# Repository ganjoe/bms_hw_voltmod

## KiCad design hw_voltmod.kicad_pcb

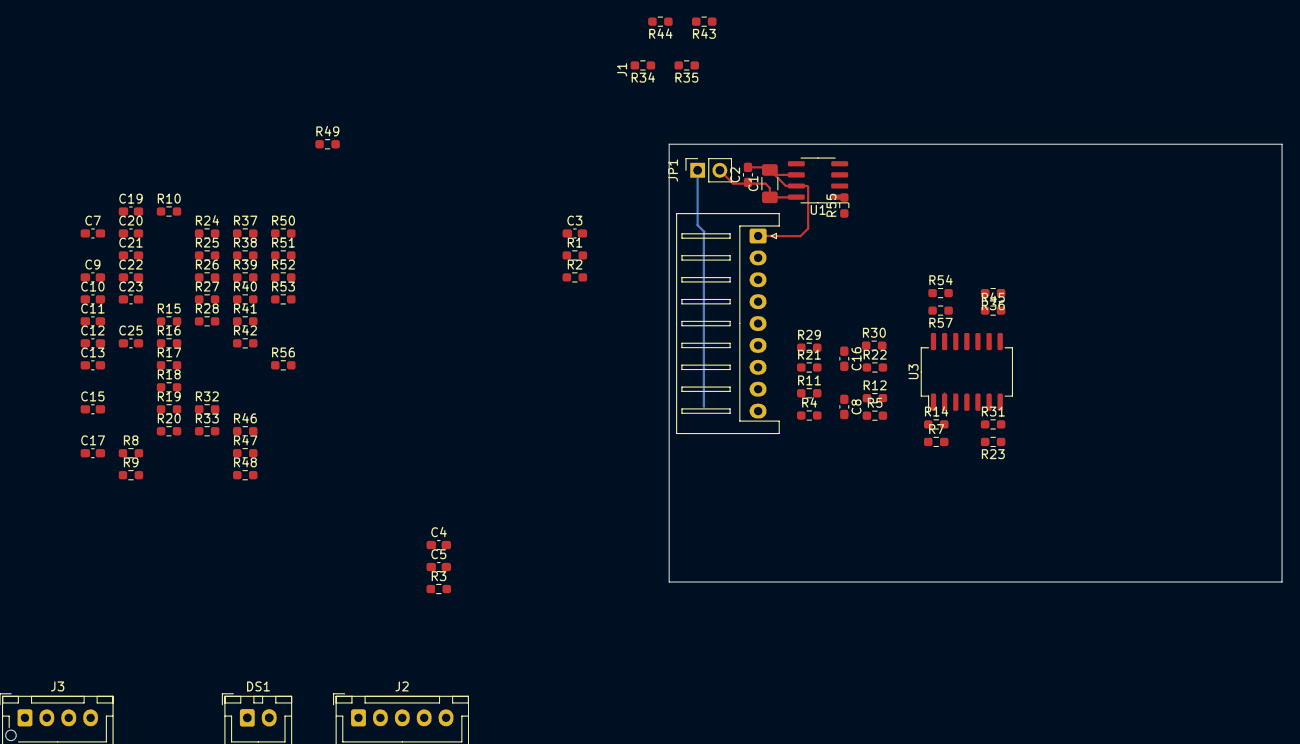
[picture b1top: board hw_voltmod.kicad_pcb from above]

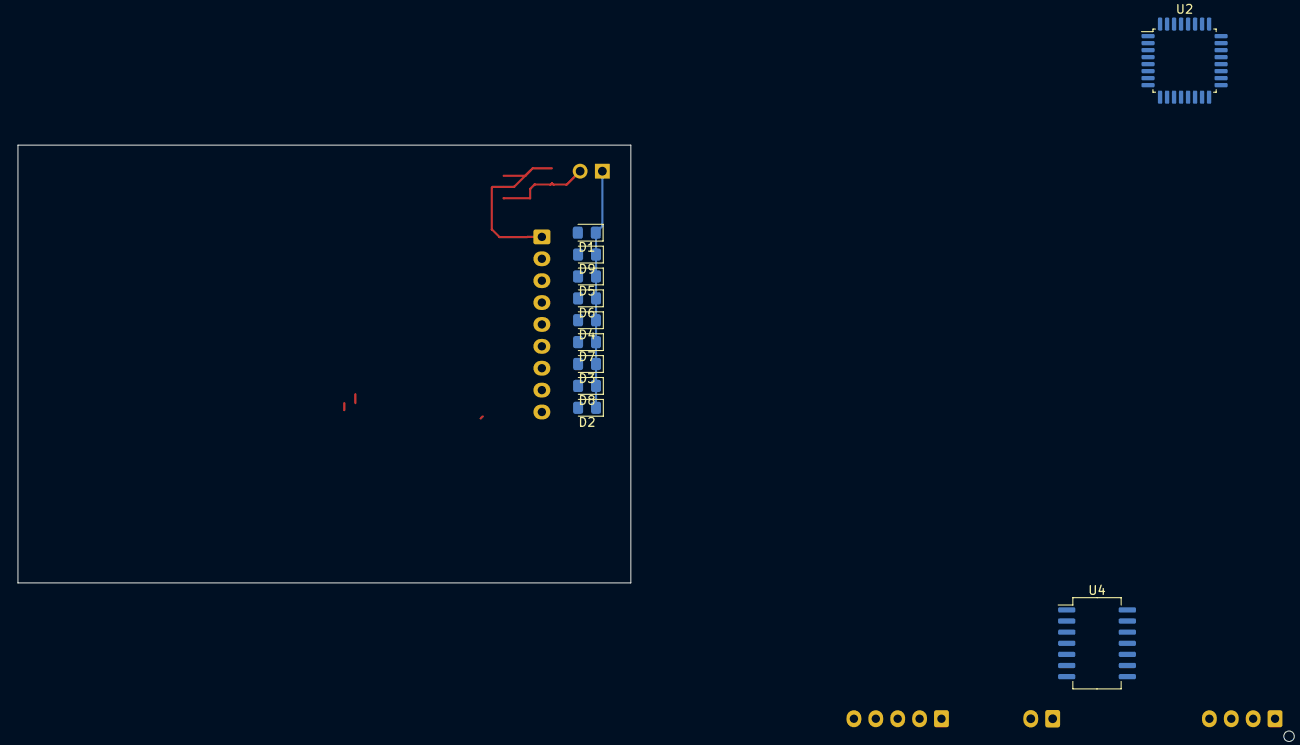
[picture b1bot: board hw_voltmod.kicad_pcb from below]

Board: 2 copper layers, 70.0 x 50.0 mm, 94 parts (11 on the bottom side), 59 nets.

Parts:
C1: 1u; C_1206_3216Metric_Pad1.33x1.80mm_HandSolder
C2, C3, C4, C7, C8, C9, C10, C12, C13, C15, C16, C17, C19, C20, C21, C22, C23, C25: 100n; C_0603_1608Metric_Pad1.08x0.95mm_HandSolder
C5: 1n; C_0603_1608Metric_Pad1.08x0.95mm_HandSolder
C11: 100p; C_0603_1608Metric_Pad1.08x0.95mm_HandSolder
D1, D2, D3, D4, D5, D6, D7, D8, D9: BAT41; D_0805_2012Metric_Pad1.15x1.40mm_HandSolder
DS1: Conn_01x02_Pin; JST_XH_B2B-XH-A_1x02_P2.50mm_Vertical
J1: Conn_01x09_Pin; JST_XH_S9B-XH-A_1x09_P2.50mm_Horizontal
J2: Conn_01x05_Pin; JST_XH_B5B-XH-A_1x05_P2.50mm_Vertical
J3: Conn_01x04_Pin; JST_XH_B4B-XH-AM_1x04_P2.50mm_Vertical
JP1: 2S; PinSocket_1x02_P2.54mm_Vertical
R1, R2: 0; R_0603_1608Metric_Pad0.98x0.95mm_HandSolder
R3: 4k7; R_0603_1608Metric_Pad0.98x0.95mm_HandSolder
R4, R5, R7, R11, R12, R14: 100k; R_0603_1608Metric_Pad0.98x0.95mm_HandSolder
R8, R9, R10, R15, R16, R17, R18, R19, R20, R21, R22, R23, R26, R27, R28, R29, R30, R31, R34, R35, R36, R37, R38, R39, R40, R41, R42, R43, R44, R45, R46, R47, R48, R49, R50, R51, R52, R53, R54, R55, R56, R57: 56k; R_0603_1608Metric_Pad0.98x0.95mm_HandSolder
R24: 18k; R_0603_1608Metric_Pad0.98x0.95mm_HandSolder
R25: 62k; R_0603_1608Metric_Pad0.98x0.95mm_HandSolder
R32: 3.9k; R_0603_1608Metric_Pad0.98x0.95mm_HandSolder
R33: 82k; R_0603_1608Metric_Pad0.98x0.95mm_HandSolder
U1: L78L33_SO8; SOIC-8_3.9x4.9mm_P1.27mm
U2: STM32G071KBTx; LQFP-32_7x7mm_P0.8mm
U3, U4: TL074; SO-14_5.3x10.2mm_P1.27mm

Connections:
+3V3: C3.1, C4.1, C5.1, J2.2, J3.1, R3.2, U1.1 (OUT), U2.4 (VDD)
+5V: D1.2 (A), J2.1
/Level Shifter/cell1: D9.2 (A), J1.2, R40.1, R46.1
/Level Shifter/cell1_amp: C20.1, R51.2, U2.8 (PA1), U4.14
/Level Shifter/cell2: D5.2 (A), J1.3, R26.1, R37.1
/Level Shifter/cell2_amp: C19.1, R48.2, U2.9 (PA2), U4.8
/Level Shifter/cell3: D6.2 (A), J1.4, R15.1, R18.1
/Level Shifter/cell3_amp: C13.1, R28.2, U2.10 (PA3), U4.7
/Level Shifter/cell4: D4.2 (A), J1.5, R8.1, R55.1
/Level Shifter/cell4_amp: C7.1, R17.2, U2.11 (PA4), U4.1
/Level Shifter/cell5: D7.2 (A), J1.6, R43.1, R52.1
/Level Shifter/cell5_amp: R57.2, U2.12 (PA5), U3.14
/Level Shifter/cell6: D3.2 (A), J1.7, R29.1, R34.1
/Level Shifter/cell6_amp: R45.2, U2.13 (PA6), U3.8
/Level Shifter/cell7: D8.2 (A), J1.8, R11.1, R21.1
/Level Shifter/cell7_amp: R31.2, U2.14 (PA7), U3.7
/Level Shifter/cell8: D2.2 (A), J1.9, R4.1, R24.1, R25.1
/Level Shifter/cell8_amp: R14.1, U2.18 (PA8), U3.1
/Level Shifter/cell_pack: C17.2, R24.2, R25.2, R32.1, R33.1, U2.7 (PA0)
/MCU/USART_PICO: R1.1, U2.22 (PA11/PA9)
/MCU/USART_POCI: R2.2, U2.23 (PA12/PA10)
/ONEWIRE: DS1.1, R3.1, U2.17 (PB2)
/USART_PICO: J3.3, R1.2
/USART_POCI: J3.2, R2.1
GNDD: C1.2, C2.2, C3.2, C4.2, C5.2, C10.1, C11.1, C12.1, C17.1, DS1.2, J1.1, J2.5, J3.4, R7.1, R10.1, R20.1, R23.1, R32.2, R33.2, R36.1, R39.1, R42.1, R49.1, R54.1, U1.2 (GND), U1.3 (GND), U1.6 (GND), U1.7 (GND), U2.5 (VSS), U3.11 (V-), U4.11 (V-)
unnamed: C7.2, C9.2, R8.2, R9.1
unnamed: C8.1, R11.2, R12.1
unnamed: C8.2, R4.2, R5.1
unnamed: C9.1, R15.2, R16.1
unnamed: C13.2, C15.2, R18.2, R19.1
unnamed: C15.1, R26.2, R27.1
unnamed: C16.1, R29.2, R30.1
unnamed: C16.2, R21.2, R22.1
unnamed: C19.2, C22.2, R37.2, R38.1
unnamed: C20.2, C23.2, R40.2, R41.1
unnamed: C21.1, R43.2, R44.1
unnamed: C21.2, R34.2, R35.1
unnamed: C22.1, R46.2, R47.1
unnamed: C23.1, R49.2, R50.1
unnamed: C25.1, R55.2, R56.1
unnamed: C25.2, R52.2, R53.1
unnamed: D1.1 (K), D2.1 (K), D3.1 (K), D4.1 (K), D5.1 (K), D6.1 (K), D7.1 (K), D8.1 (K), D9.1 (K), JP1.1 (A)
unnamed: R5.2, R7.2, U3.3 (+)
unnamed: R12.2, R14.2, U3.2 (-)
unnamed: R22.2, R23.2, U3.5 (+)
unnamed: R30.2, R31.1, U3.6 (-)
unnamed: R35.2, R36.2, U3.10 (+)
unnamed: R44.2, R45.1, U3.9 (-)
unnamed: R53.2, R54.2, U3.12 (+)
unnamed: R56.2, R57.1, U3.13 (-)
unnamed: R9.2, R10.2, U4.3 (+)
unnamed: R16.2, R17.1, U4.2 (-)
unnamed: R19.2, R20.2, U4.5 (+)
unnamed: R27.2, R28.1, U4.6 (-)
unnamed: R38.2, R39.2, U4.10 (+)
unnamed: R47.2, R48.1, U4.9 (-)
unnamed: R41.2, R42.2, U4.12 (+)
unnamed: R50.2, R51.1, U4.13 (-)
VBUS: C1.1, C2.1, C10.2, C11.2, C12.2, JP1.2 (B), U1.8 (IN), U3.4 (V+), U4.4 (V+)

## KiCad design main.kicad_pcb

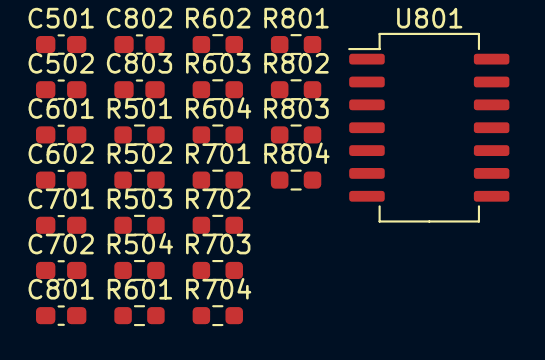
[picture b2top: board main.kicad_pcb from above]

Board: 2 copper layers, 26 parts (0 on the bottom side), 18 nets, no tracks yet.

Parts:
C501, C502, C601, C602, C701, C702, C801, C802, C803: 100n; C_0603_1608Metric_Pad1.08x0.95mm_HandSolder
R501, R502, R503, R504, R601, R602, R603, R604, R701, R702, R703, R704, R801, R802, R803, R804: 56k; R_0603_1608Metric_Pad0.98x0.95mm_HandSolder
U801: TL074; SO-14_5.3x10.2mm_P1.27mm

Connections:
unnamed: R501.2, R502.2, U801.3 (+)
unnamed: C502.1, R503.2, R504.1, U801.2 (-)
unnamed: R601.2, R602.2, U801.5 (+)
unnamed: C602.1, R603.2, R604.1, U801.6 (-)
unnamed: R701.2, R702.2, U801.10 (+)
unnamed: C702.1, R703.2, R704.1, U801.9 (-)
unnamed: R801.2, R804.2, U801.12 (+)
unnamed: C802.1, R802.2, R803.1, U801.13 (-)
cell0: C803.1, R502.1, R602.1, R702.1, R804.1, U801.11 (V-)
cell4: C501.1, R503.1
cell5: C501.2, C601.1, R501.1, R603.1
cell5_amp: C502.2, R504.2, U801.1
cell6: C601.2, C701.1, R601.1, R703.1
cell6_amp: C602.2, R604.2, U801.7
cell7: C701.2, C801.1, R701.1, R802.1
cell7_amp: C702.2, R704.2, U801.8
cell8: C801.2, C803.2, R801.1, U801.4 (V+)
cell8_amp: C802.2, R803.2, U801.14

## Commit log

2023-03-25 githubstart
2023-03-25 capacitor added to ldr
2023-03-25 colors
2023-03-25 simu
2023-03-26 asdf
2023-03-26 tzutz
2023-03-27 aisler DRC und preise
